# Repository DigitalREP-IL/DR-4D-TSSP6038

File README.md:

The DR-4 LRIR is a longer range reflective distance sensor showcasing the Vishay TSSP6038. The TSSP6038 includes a signal conditioning section to demodulate a 38kHz carrier for light source disturbance immunity (for example, changing sunlight or fluorescent illumination). An IR emitter and support circuitry complete this sensor evaluation solution. Two options are available for either a simple digital signal output (TSSP6038), or a variable pulsewidth "analog" output (TSSP6P38).

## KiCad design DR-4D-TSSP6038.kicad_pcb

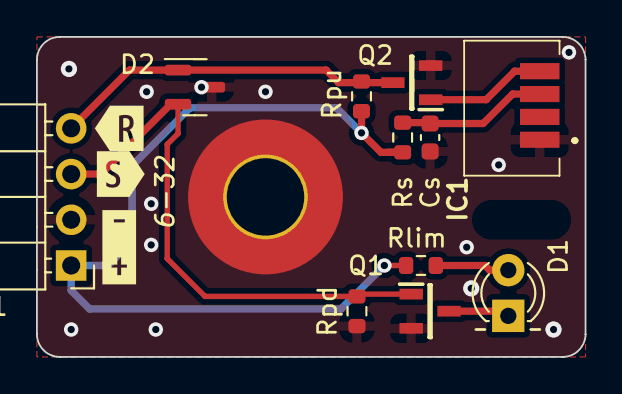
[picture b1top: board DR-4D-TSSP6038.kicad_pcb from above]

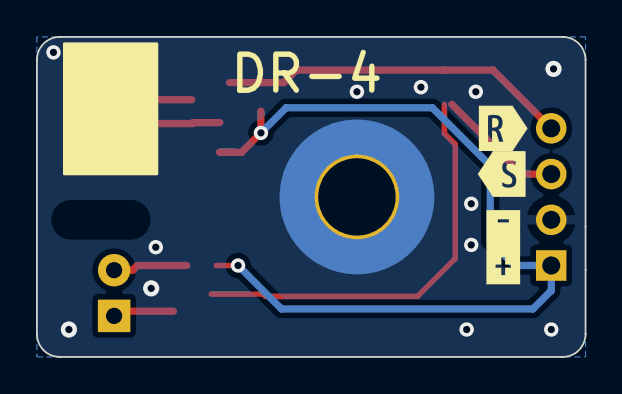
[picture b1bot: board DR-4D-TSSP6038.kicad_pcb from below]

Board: 2 copper layers, 30.5 x 17.8 mm, 20 parts (4 on the bottom side), 8 nets.

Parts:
Cs: .47u; C_0603_1608Metric
D1: VLSB4940; LED_D3.0mm_IRBlack
D2: SP0502BAHT; SOT-23
H1: 6-32; MountingHole_4.3mm_M4_Pad_TopBottom
H2: MountingHole; MountingHole_2.1mm
IC1: TSSP6038TR
J1: Conn_01x04; PinHeader_1x04_P2.54mm_Horizontal
LOGO1: LOGO; tinyrep
Q1: Si2302CDS-T1-GE3; SOT95P237X112-3N
Q2: SI2302CDS-T1-GE3; SOT95P237X112-3N
Rlim: 91R; R_0603_1608Metric
Rpd: 10K0; R_0603_1608Metric
Rpu: 1k0; R_0603_1608Metric
Rs: 91R; R_0603_1608Metric
kibuzzard-637672C4: G***; kibuzzard-637672C4
kibuzzard-6376729D: G***; kibuzzard-6376729D
kibuzzard-63767288: G***; kibuzzard-63767288
kibuzzard-63767574: G***; kibuzzard-63767574
kibuzzard-63767584: G***; kibuzzard-63767584
kibuzzard-63767593: G***; kibuzzard-63767593

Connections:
/R: D2.1 (K), J1.4, Q2.3, Rpu.2
/S: D2.2 (K), J1.3, Q1.1, Rpd.1
GND: Cs.2, D2.3 (A), H1.1, IC1.1 (GND), J1.2, Q1.2, Q2.2, Rpd.2
unnamed: D1.2 (A), Rlim.2
unnamed: D1.1 (K), Q1.3
unnamed: IC1.4 (OUT), Q2.1
unnamed: Cs.1, IC1.3 (VS), Rs.1
VS: J1.1, Rlim.1, Rpu.1, Rs.2

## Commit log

2024-03-20 adding schematic print
